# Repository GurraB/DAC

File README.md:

# DAC
A USB DAC

This is my take on an USB DAC. 

Theoretical specs:
- 16 bit resolution
- fs = 44.1 kHz
- Signal to noise ratio: 127 dB
- THD+N: 0.0004%

Components:

- TI PCM2707c http://www.ti.com/lit/ds/sbfs036b/sbfs036b.pdf
- TI PCM1794a http://www.ti.com/lit/ds/symlink/pcm1794a.pdf
- TI OPA2134 http://www.ti.com/lit/ds/symlink/opa2134.pdf
- TI LM2662 http://www.ti.com/lit/ds/symlink/lm2663.pdf
- TI TPS60501 http://www.ti.com/lit/ds/symlink/tps60500.pdf

This was designed in EAGLE CAD. It is the first PCB I have ever made. The PCM2707c is used as an USB interface, it is automatically detected as a DAC by windows (Linux might need some drivers). The PCM2707c converts the USB signal to i2s and sends it to the PCM1794a. PCM1794a is a high quality DAC that generates the output signal. The signal is then sent to the operational amplifier.

The bottleneck in the system is the PCM2707c since it can only accept 16 bit audio signal.

Future work:
This is the first design that I have made to see if I can make a simple DAC to begin with. In the future I have plans to add an ESP32 to allow for bluetooth connectivity. I have also thought about adding a Raspberry Pi Zero W that can act as a spotify connect device.

Design is based upon http://users.abo.fi/jskata/JEDAC/

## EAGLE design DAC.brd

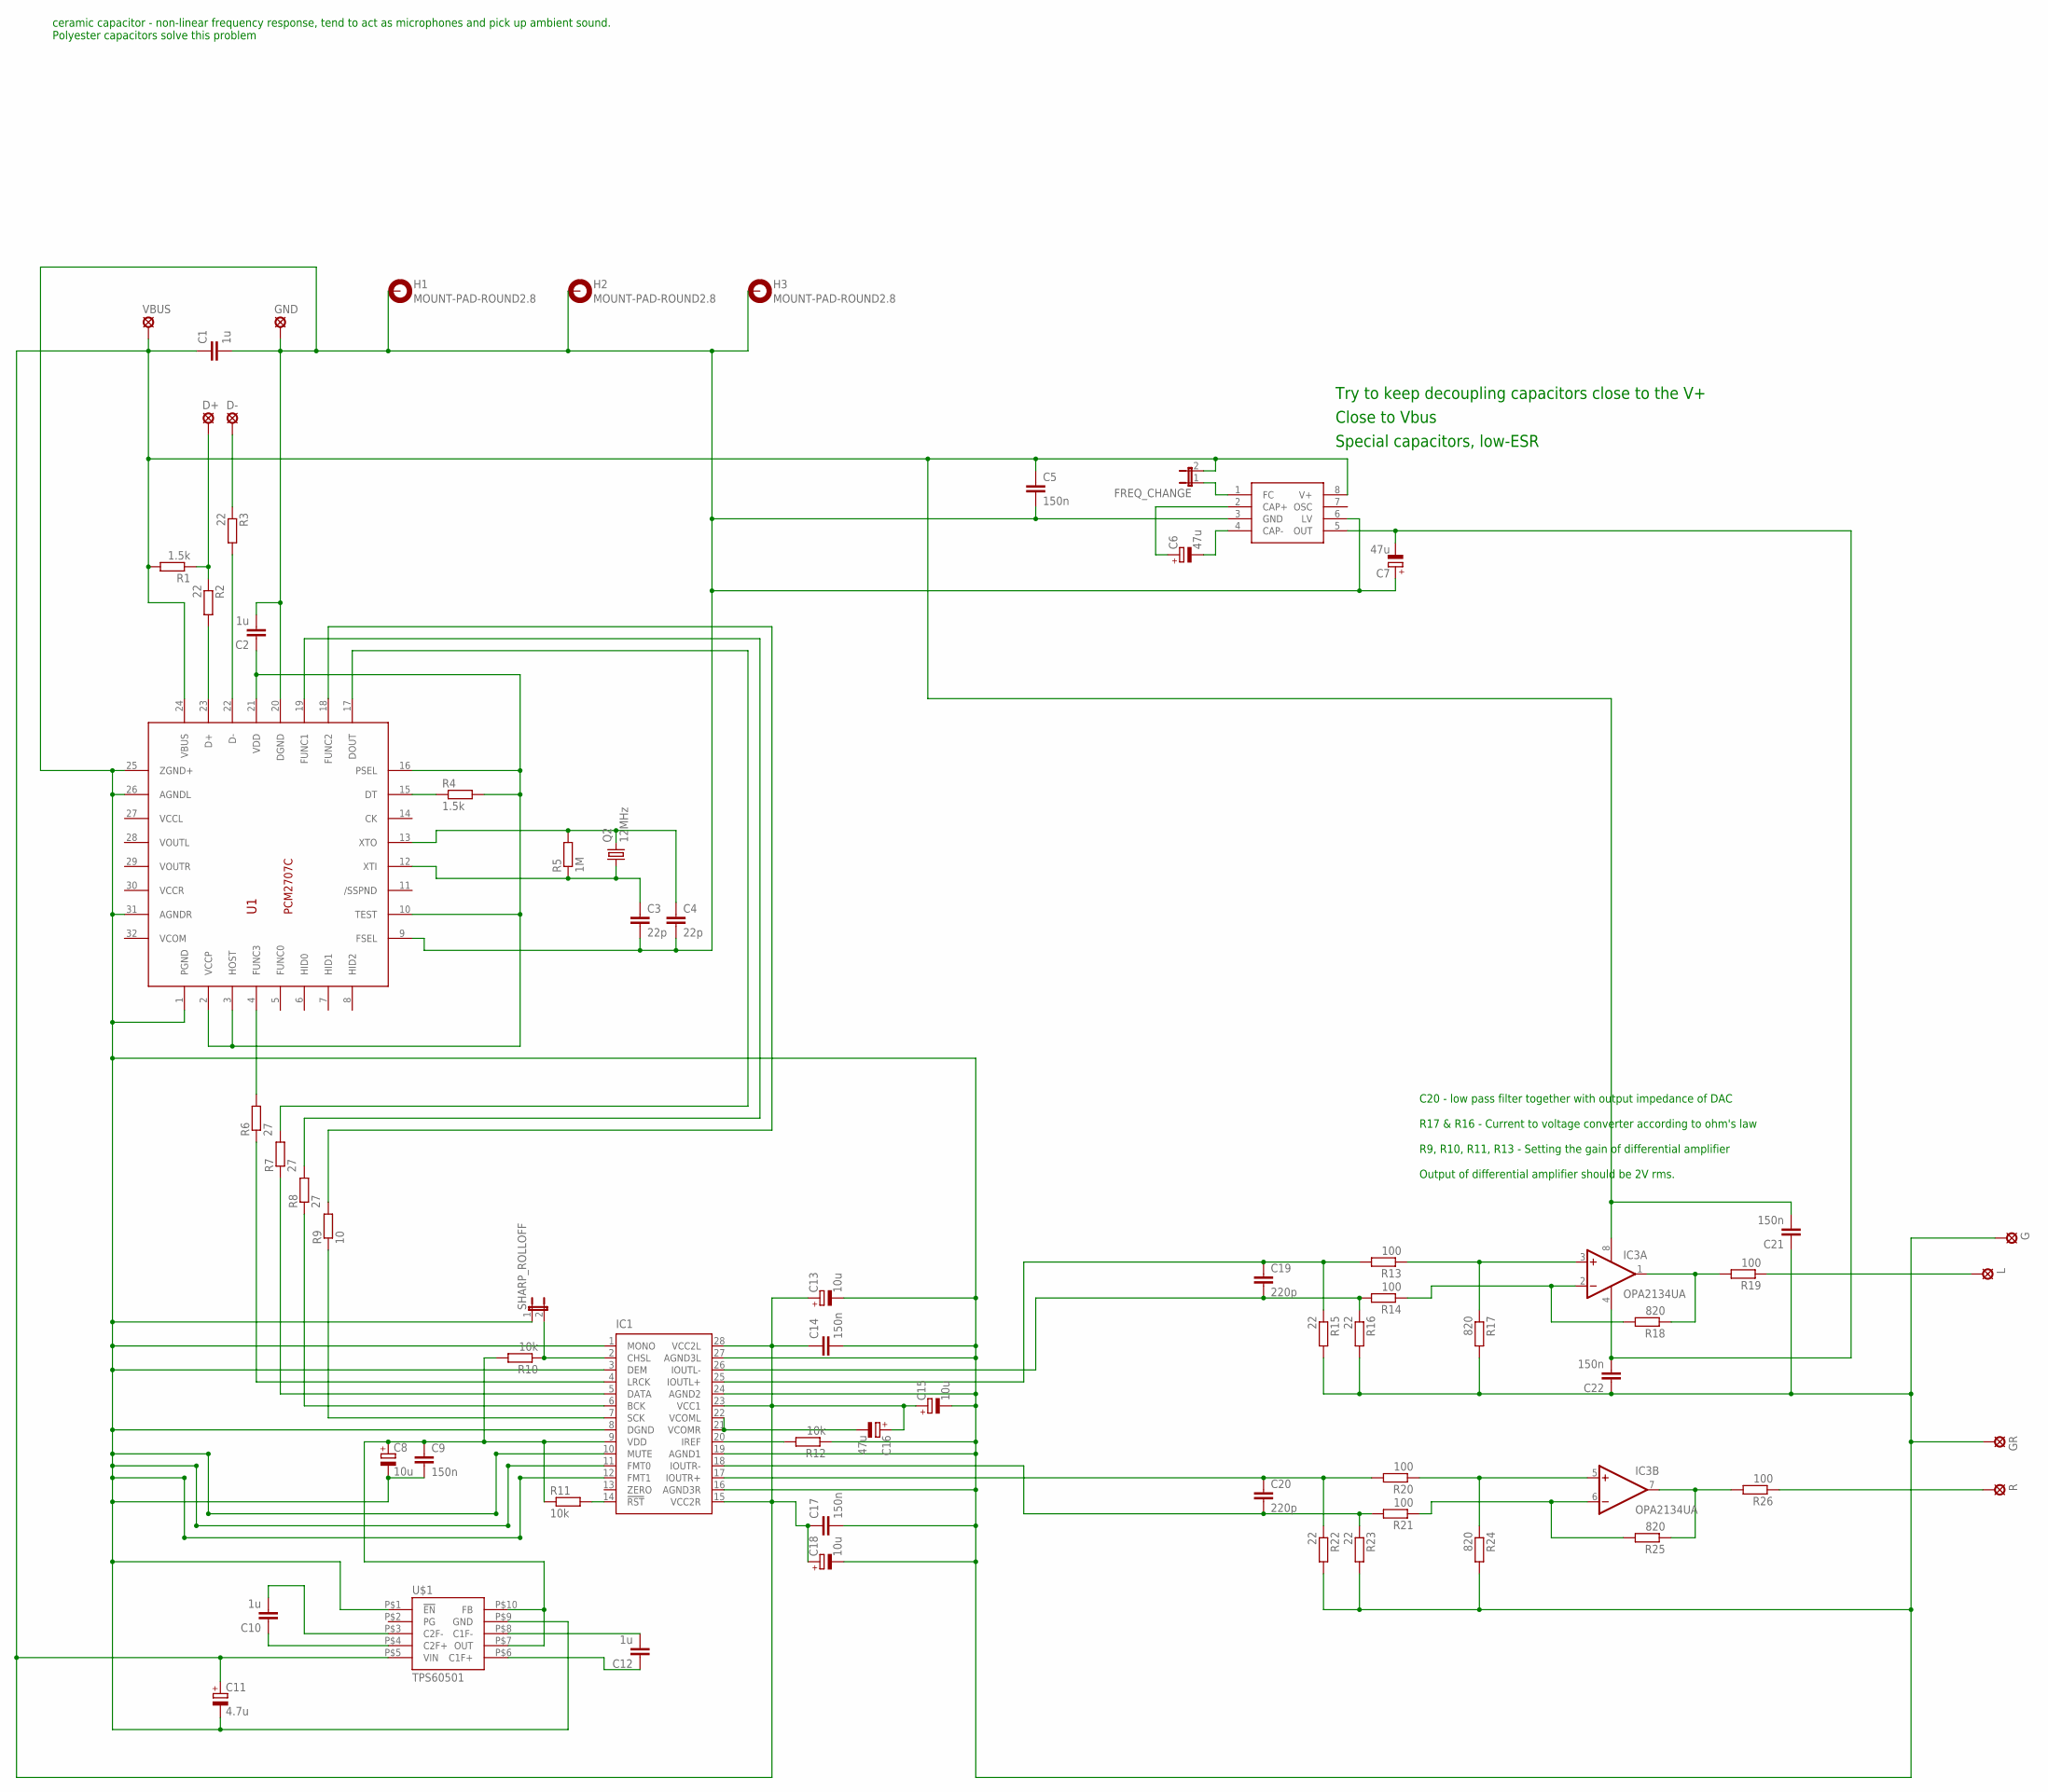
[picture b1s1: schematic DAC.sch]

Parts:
C1, C2, C10, C12: 1u; C050-050X075
C3, C4: 22p; C0603
C5, C9, C14, C17, C21, C22: 150n; C050-025X075
C6, C7: 47u; PANASONIC_D
C8: 10u; 153CLV-0405
C11: 4.7u; E2-5
C13, C15, C18: 10u; E2-5
C16: 47u; E2-5
C19, C20: 220p; C025-024X044
D+: LSP10
D-: LSP10
FREQ_CHANGE: JP1E; JP1
G: LSP10
GND: LSP10
GR: LSP10
H1, H2, H3: MOUNT-PAD-ROUND2.8; 2,8-PAD
IC1: PCM1794A; SSOP28DB
IC3: OPA2134UA; SO08
L: LSP10
Q2: 12MHz; HC49/S
R: LSP10
R1, R4: 1.5k; R0603
R2, R3: 22; R0603
R5: 1M; R0603
R6, R7, R8: 27; R0603
R9: 10; R0603
R10, R11: 10k; R0603
R12: 10k; 0207/10
R13, R14, R19, R20, R21, R26: 100; 0207/10
R15, R16, R22, R23: 22; 0207/10
R17, R18, R24, R25: 820; 0207/10
SHARP_ROLLOFF: JP1E; JP1
U1: PCM2707C; 32TQFP_PCM2707C
U$1: TPS60501; VSSOP10
U$2: LM2662; SOIC8
VBUS: LSP10

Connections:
D+: D+.MP, R1.1, R2.1
D-: D-.MP, R3.1
GND: C1.2, C2.2, C3.2, C4.2, C5.2, C7.+, C8.-, C9.2, C11.-, C13.-, C14.2, C15.-, C17.2, C18.-, C21.1, C22.1, G.MP, GND.MP, GR.MP, H1.B2,8, H2.B2,8, H3.B2,8, IC1.1 (MONO), IC1.3 (DEM), IC1.8 (DGND), IC1.10 (MUTE), IC1.11 (FMT0), IC1.12 (FMT1), IC1.16 (AGND3R), IC1.19 (AGND1), IC1.24 (AGND2), IC1.27 (AGND3L), R12.1, R15.2, R16.2, R17.2, R22.2, R23.2, R24.2, SHARP_ROLLOFF.1, U1.1 (PGND), U1.9 (FSEL), U1.20 (DGND), U1.25 (ZGND+), U1.26 (AGNDL), U1.31 (AGNDR), U$1.P$1 (!EN), U$1.P$9 (GND), U$2.3 (GND), U$2.6 (LV)
unnamed: R2.2, U1.23 (D+)
unnamed: R3.2, U1.22 (D-)
unnamed: C2.1, R4.2, U1.2 (VCCP), U1.3 (HOST), U1.10 (TEST), U1.16 (PSEL), U1.21 (VDD)
unnamed: R4.1, U1.15 (DT)
unnamed: C4.1, Q2.2, R5.2, U1.13 (XTO)
unnamed: C3.1, Q2.1, R5.1, U1.12 (XTI)
unnamed: C10.1, U$1.P$4 (C2F+)
unnamed: C10.2, U$1.P$3 (C2F-)
unnamed: IC1.20 (IREF), R12.2
unnamed: C12.2, U$1.P$8 (C1F-)
unnamed: C6.-, U$2.4 (CAP-)
unnamed: IC1.5 (DATA), R7.1
unnamed: IC3.2 (-IN), R14.1, R18.2
unnamed: IC3.7 (OUT), R25.1, R26.2
unnamed: C12.1, U$1.P$6 (C1F+)
unnamed: IC1.14 (!RST), R11.2
unnamed: IC1.6 (BCK), R8.1
unnamed: IC1.2 (CHSL), R10.1, SHARP_ROLLOFF.2
unnamed: IC1.4 (LRCK), R6.1
unnamed: R7.2, U1.17 (DOUT)
unnamed: R8.2, U1.19 (FUNC1)
unnamed: R9.2, U1.18 (FUNC2)
unnamed: C19.2, IC1.26 (IOUTL-), R14.2, R16.1
unnamed: C19.1, IC1.25 (IOUTL+), R13.2, R15.1
unnamed: C20.1, IC1.17 (IOUTR+), R20.2, R22.1
unnamed: C20.2, IC1.18 (IOUTR-), R21.2, R23.1
unnamed: IC3.6 (-IN), R21.1, R25.2
unnamed: IC3.1 (OUT), R18.1, R19.2
unnamed: FREQ_CHANGE.1, U$2.1 (FC)
unnamed: C6.+, U$2.2 (CAP+)
unnamed: IC3.3 (+IN), R13.1, R17.1
unnamed: C16.-, IC1.21 (VCOMR), IC1.22 (VCOML)
unnamed: L.MP, R19.1
unnamed: IC3.5 (+IN), R20.1, R24.1
unnamed: C1.1, C5.1, C11.+, C13.+, C14.1, C15.+, C16.+, C17.1, C18.+, C21.2, FREQ_CHANGE.2, IC1.15 (VCC2R), IC1.23 (VCC1), IC1.28 (VCC2L), IC3.8 (V+), R1.2, U1.24 (VBUS), U$1.P$5 (VIN), U$2.8 (V+), VBUS.MP
unnamed: C8.+, C9.1, IC1.9 (VDD), R10.2, R11.1, U$1.P$7 (OUT), U$1.P$10 (FB)
unnamed: R.MP, R26.1
unnamed: IC1.7 (SCK), R9.1
unnamed: R6.2, U1.4 (FUNC3)
NEG_VOLTAGE: C7.-, C22.2, IC3.4 (V-), U$2.5 (OUT)

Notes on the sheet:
Close to Vbus
Special capacitors, low-ESR
Try to keep decoupling capacitors close to the V+
C20 - low pass filter together with output impedance of DAC R17 & R16 - Current to voltage converter according to ohm's law R9, R10, R11, R13 - Setting the gain of differential amplifier Output of differential amplifier should be 2V rms.
ceramic capacitor - non-linear frequency response, tend to act as microphones and pick up ambient sound. Polyester capacitors solve this problem

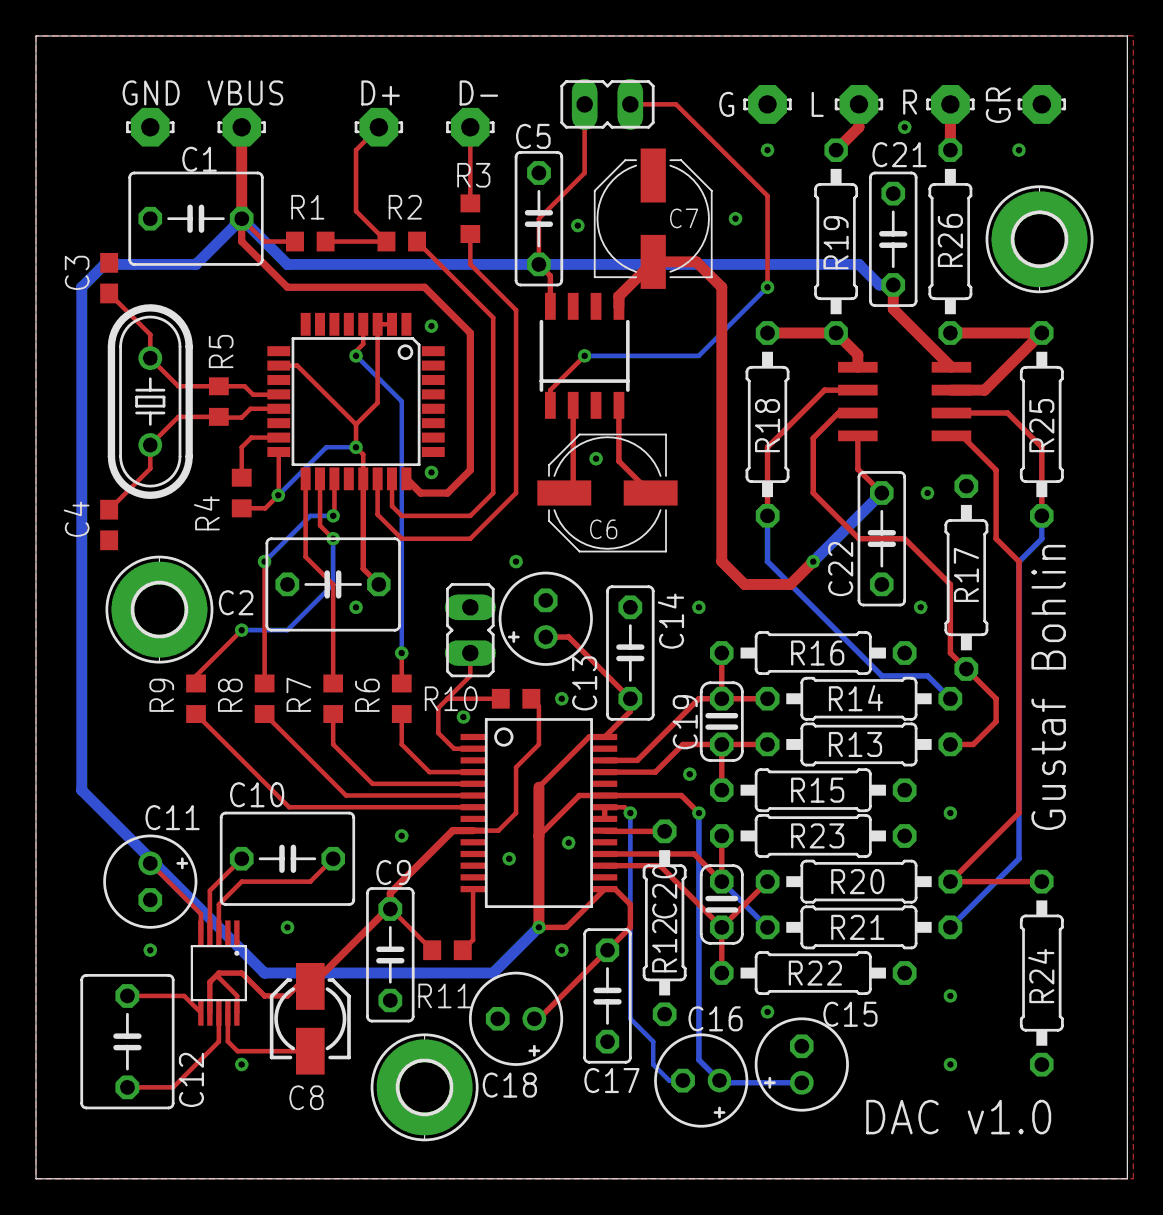
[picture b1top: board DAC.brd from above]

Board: 2 copper layers, 60.6 x 63.5 mm, 67 parts (0 on the bottom side), 43 nets.

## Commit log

2018-02-25 Added README
2018-02-25 Uploaded EAGLE files and pictures
2018-02-25 Added pictures of board
2018-03-03 Updated status
2018-09-17 Added images of finished project
